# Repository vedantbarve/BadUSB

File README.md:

# Disclamer

This project is for educational purpose only. Do not execute this attack on anyone without their consent.

# BadUSB

In this world full of cyberattacks, humans are the weakest links to break into a system. The USB rubber ducky or BadUSB is a malicious tool, which when inserted into a system will inject keyboard strokes as if it is an HID (Human Interface Device like keyboard, mouse, game controller etc.).

In this project, I have used Attiny85 as the microcontroller of choice as it is cheap, compact and versatile. This project builds the BadUSB from ground up i.e we will be making the USB, flashing the bootloader, writing a script that runs when we insert the pendrive into the victim's machine and the payload that runs at the client side which compromises the system. This project initiates a reverse shell connection from the victim to the attacker to gain command line access of the victim's machine.

## Aim of the project

1. Run a powershell script on a windows machine after inserting the USB rubber ducky.
2. Initiate a reverse shell connection from the victim to the attacker to gain command line access of the victim's machine.

## Contents

| Sr. No. | Title           | Description                                                                                             |
| ------- | --------------- | ------------------------------------------------------------------------------------------------------- |
| 1.      | badusb-script   | The script that runs when the USB is inserted into the victim's machine.                                |
| 2.      | badusb-programs | The payloads written in GO that establish the reverse-shell connection from the victim to the attacker. |

## Motivation

In an ordinary cyberattack, an attacker tries to find vulnerabilities in the victim's machine by monitoring them over the network. With newer IDS and IPS techniques, it is quite difficult to penetrate a system when an attacker tries to connect with the victim.  
On the other hand, the attacker can make changes on its machine to listen and accept for incoming connections. So if we make the victim connect to the attacker, there are no restrictions by the firewall.  
Thus, a reverse shell attack seemed perfect for this usecase.

## Methodology

** Socket server port and HTTP server port are changed to :9999 and :9998 respectively, while migrating from C++ to GO.

After the USB rubber ducky is inserted into the victim's machine, following steps take place:

1. Keyboard stokes open powershell and use the curl command to download the payload (client.exe) from the "/" endpoint on the HTTP server hosted on PORT=9998 on the attacker's IP address.
2. We run the client.exe file.
3. On running the client.exe file, victim's machine initiates a connection with the attacker who is listening for incoming connections on its PORT=9999.
4. Once the attacker accepts the incoming connection, we can start exchanging data.

## Softwares used

1. ArduinoIDE :
   - To flash bootloader onto the Attiny85.
   - To burn the script that runs after inserting the USB.
2. KiCAD :
   - To design the PCB for the USB.
3. VScode :
   - To make the GO payload.

## Future scope

This project can be made dynamic by adding payloads for operating systems other than windows. We can send the OS data from the victim to the attacker first, so that the HTTP server will respond with appropriate payload.

## Images

[Rubber Ducky Video](https://github.com/vedantbarve/BadUSB/blob/master/assets/bb3333ab-b4e2-4a25-af28-9a1edc2237c5.mov)
## Contact me

Please feel free to contact me via the email given below for any doubts. I am always open for any sort of constructive criticism.

Email :- barvevedant@gmail.com

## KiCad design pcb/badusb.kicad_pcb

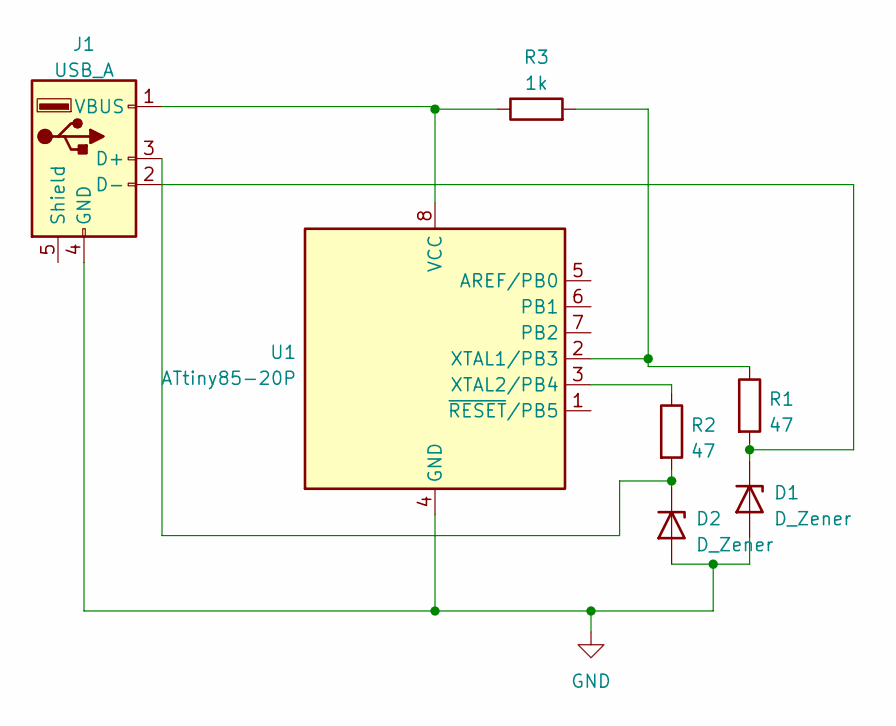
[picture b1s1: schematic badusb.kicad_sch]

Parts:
D1, D2: D_Zener; D_DO-15_P12.70mm_Horizontal
J1: USB_A; USB_A_CONNFLY_DS1095-WNR0
R1, R2: 47; R_Axial_DIN0411_L9.9mm_D3.6mm_P12.70mm_Horizontal
R3: 1k; R_Axial_DIN0411_L9.9mm_D3.6mm_P12.70mm_Horizontal
U1: ATtiny85-20P; DIP-8_W7.62mm

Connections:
GND: D1.2 (A), D2.2 (A), J1.4 (GND), U1.4 (GND)
unnamed: D1.1 (K), J1.2 (D-), R1.2
unnamed: D2.1 (K), J1.3 (D+), R2.2
unnamed: J1.1 (VBUS), R3.1, U1.8 (VCC)
unnamed: R1.1, R3.2, U1.2 (XTAL1/PB3)
unnamed: R2.1, U1.3 (XTAL2/PB4)

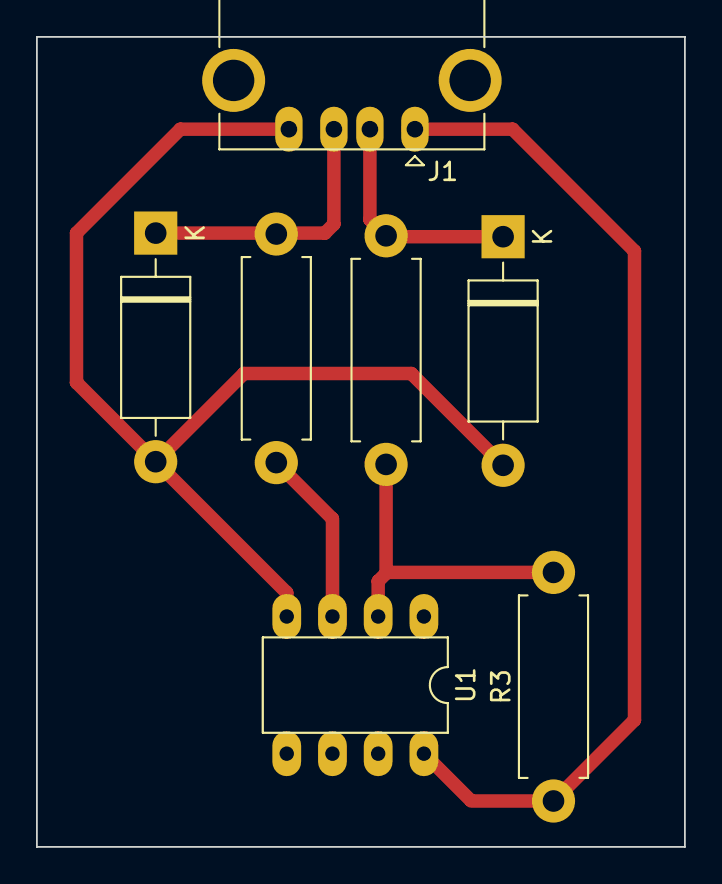
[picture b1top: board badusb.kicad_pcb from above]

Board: 2 copper layers, 36.0 x 45.0 mm, 7 parts (0 on the bottom side), 6 nets.

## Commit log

2024-04-02 add readme to every section
2024-04-14 add gitignore
2024-04-14 bootloader
2024-08-31 migrate to GO
2024-09-12 add comments to client.go
2024-09-12 add comments to the code
2024-09-19 execute client tasks as goroutines
